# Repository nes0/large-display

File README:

PCB layout for a nominally 100mm 14 or 7 segment display including a PWM capable driver.

https://github.com/nes0/large-display

Licenced under "CERN Open Hardware Licence Version 2 - Weakly Reciprocal" http://ohwr.org/cernohl. Also see "cern_ohl_w_v2.txt"

No warranty is provided for this documentation implied or otherwise.

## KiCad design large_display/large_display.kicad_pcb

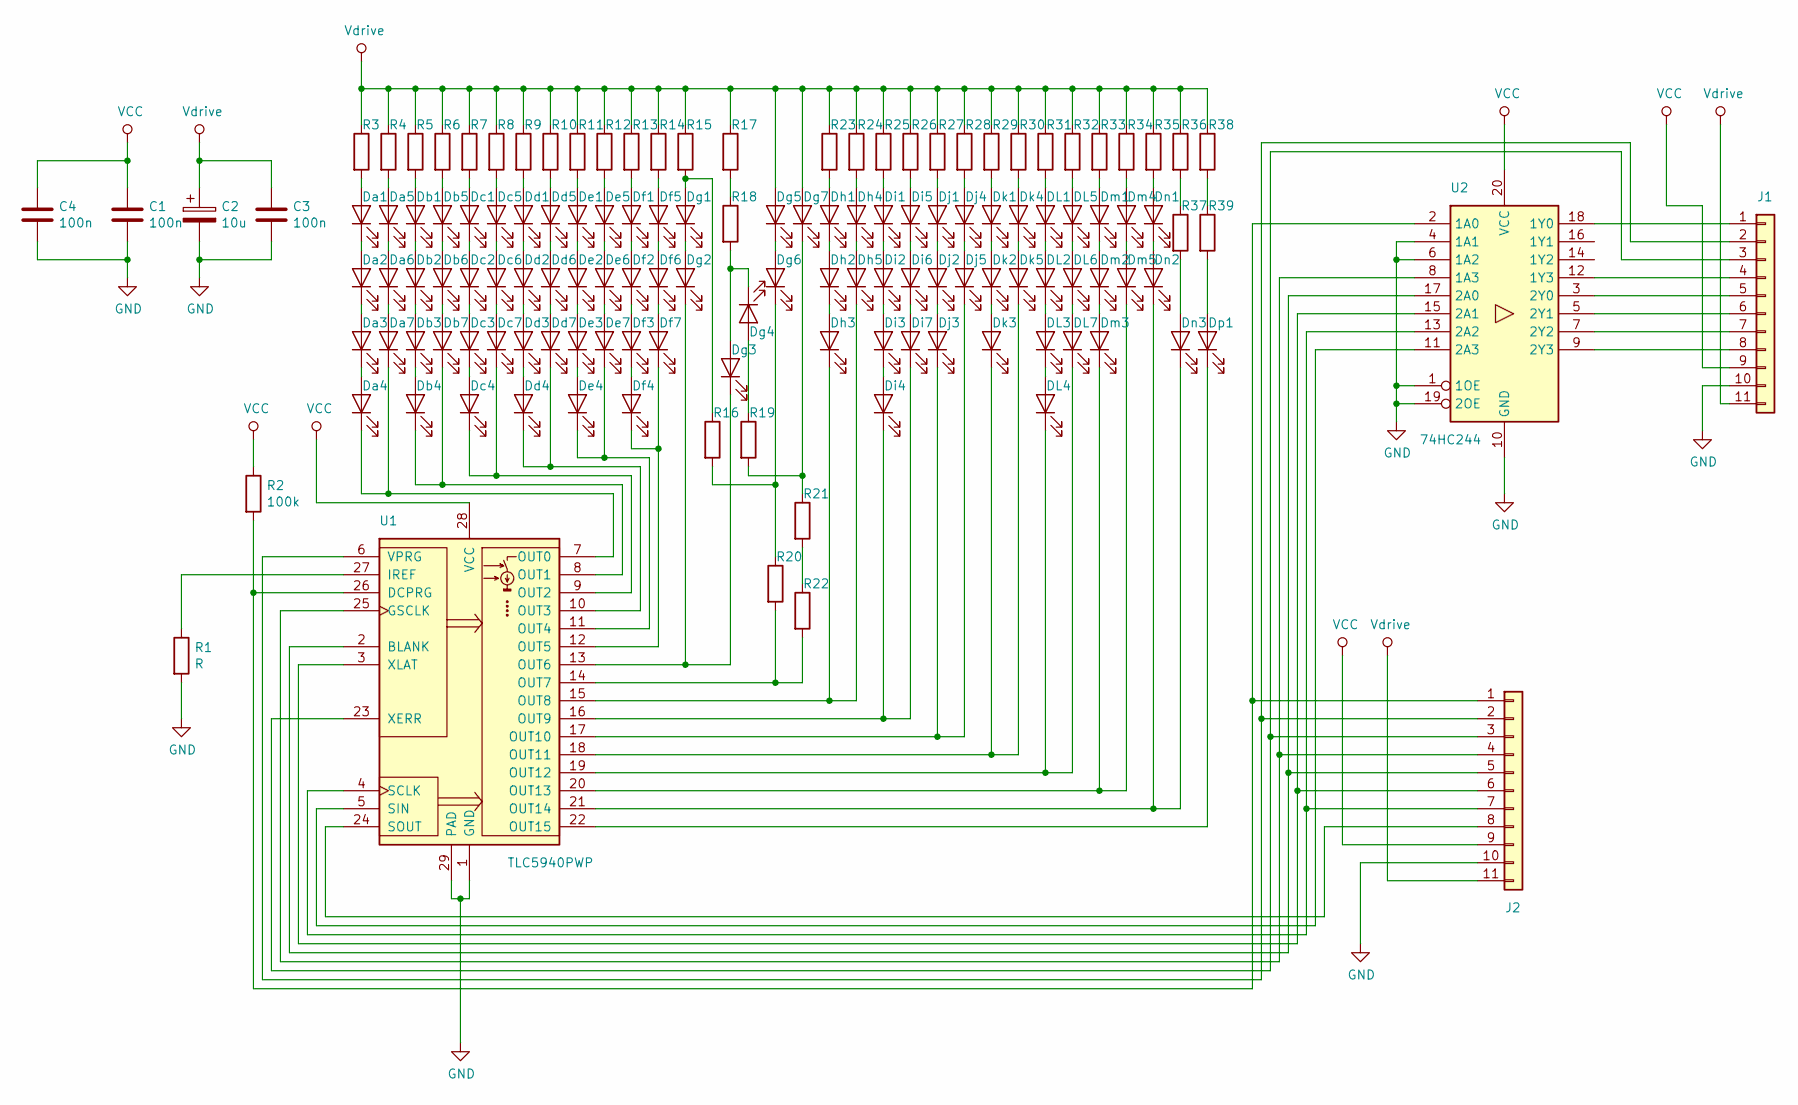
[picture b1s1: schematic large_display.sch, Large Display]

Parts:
C1, C3, C4: 100n; C_0805_2012Metric
C2: 10u; CP_Elec_6.3x4.5
DL1, DL2, DL3, DL4, DL5, DL6, DL7: LED; LED_PLCC_2835_Handsoldering
Da1, Da2, Da3, Da4, Da5, Da6, Da7: LED; LED_PLCC_2835_Handsoldering
Db1, Db2, Db3, Db4, Db5, Db6, Db7: LED; LED_PLCC_2835_Handsoldering
Dc1, Dc2, Dc3, Dc4, Dc5, Dc6, Dc7: LED; LED_PLCC_2835_Handsoldering
Dd1, Dd2, Dd3, Dd4, Dd5, Dd6, Dd7: LED; LED_PLCC_2835_Handsoldering
De1, De2, De3, De4, De5, De6, De7: LED; LED_PLCC_2835_Handsoldering
Df1, Df2, Df3, Df4, Df5, Df6, Df7: LED; LED_PLCC_2835_Handsoldering
Dg1, Dg2, Dg3, Dg4, Dg5, Dg6, Dg7: LED; LED_PLCC_2835_Handsoldering
Dh1, Dh2, Dh3, Dh4, Dh5: LED; LED_PLCC_2835_Handsoldering
Di1, Di2, Di3, Di4, Di5, Di6, Di7: LED; LED_PLCC_2835_Handsoldering
Dj1, Dj2, Dj3, Dj4, Dj5: LED; LED_PLCC_2835_Handsoldering
Dk1, Dk2, Dk3, Dk4, Dk5: LED; LED_PLCC_2835_Handsoldering
Dm1, Dm2, Dm3, Dm4, Dm5: LED; LED_PLCC_2835_Handsoldering
Dn1, Dn2, Dn3: LED; LED_PLCC_2835_Handsoldering
Dp1: LED; LED_PLCC_2835_Handsoldering
J1: Conn_01x11; PinHeader_1x11_P2.54mm_Horizontal
J2: Conn_01x11; PinSocket_1x11_P2.54mm_Horizontal
R1: R; R_0805_2012Metric_Pad1.15x1.40mm_HandSolder
R2: 100k; R_0805_2012Metric_Pad1.15x1.40mm_HandSolder
R3, R4, R5, R6, R7, R8, R9, R10, R11, R12, R13, R14, R15, R16, R17, R18, R19, R20, R21, R22, R23, R24, R25, R26, R27, R28, R29, R30, R31, R32, R33, R34, R35, R36, R37, R38, R39: R; R_1206_3216Metric_Pad1.42x1.75mm_HandSolder
U1: TLC5940PWP; HTSSOP-28-1EP_4.4x9.7mm_P0.65mm_EP3.4x9.5mm_Mask2.4x6.17mm_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
U2: 74HC244; SSOP-20_5.3x7.2mm_P0.65mm

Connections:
GND: C1.2, C2.2, C3.2, C4.2, J1.10, J2.10, R1.2, U1.1 (GND), U1.29 (PAD), U2.1 (1OE), U2.4 (1A1), U2.6 (1A2), U2.10 (GND), U2.19 (2OE)
unnamed: DL1.1 (K), DL2.2 (A)
unnamed: DL1.2 (A), R31.2
unnamed: DL2.1 (K), DL3.2 (A)
unnamed: DL3.1 (K), DL4.2 (A)
unnamed: DL4.1 (K), DL7.1 (K), U1.19 (OUT12)
unnamed: DL5.1 (K), DL6.2 (A)
unnamed: DL5.2 (A), R32.2
unnamed: DL6.1 (K), DL7.2 (A)
unnamed: Da1.1 (K), Da2.2 (A)
unnamed: Da1.2 (A), R3.2
unnamed: Da2.1 (K), Da3.2 (A)
unnamed: Da3.1 (K), Da4.2 (A)
unnamed: Da4.1 (K), Da7.1 (K), U1.7 (OUT0)
unnamed: Da5.1 (K), Da6.2 (A)
unnamed: Da5.2 (A), R4.2
unnamed: Da6.1 (K), Da7.2 (A)
unnamed: Db1.1 (K), Db2.2 (A)
unnamed: Db1.2 (A), R5.2
unnamed: Db2.1 (K), Db3.2 (A)
unnamed: Db3.1 (K), Db4.2 (A)
unnamed: Db4.1 (K), Db7.1 (K), U1.8 (OUT1)
unnamed: Db5.1 (K), Db6.2 (A)
unnamed: Db5.2 (A), R6.2
unnamed: Db6.1 (K), Db7.2 (A)
unnamed: Dc1.1 (K), Dc2.2 (A)
unnamed: Dc1.2 (A), R7.2
unnamed: Dc2.1 (K), Dc3.2 (A)
unnamed: Dc3.1 (K), Dc4.2 (A)
unnamed: Dc4.1 (K), Dc7.1 (K), U1.9 (OUT2)
unnamed: Dc5.1 (K), Dc6.2 (A)
unnamed: Dc5.2 (A), R8.2
unnamed: Dc6.1 (K), Dc7.2 (A)
unnamed: Dd1.1 (K), Dd2.2 (A)
unnamed: Dd1.2 (A), R9.2
unnamed: Dd2.1 (K), Dd3.2 (A)
unnamed: Dd3.1 (K), Dd4.2 (A)
unnamed: Dd4.1 (K), Dd7.1 (K), U1.10 (OUT3)
unnamed: Dd5.1 (K), Dd6.2 (A)
unnamed: Dd5.2 (A), R10.2
unnamed: Dd6.1 (K), Dd7.2 (A)
unnamed: De1.1 (K), De2.2 (A)
unnamed: De1.2 (A), R11.2
unnamed: De2.1 (K), De3.2 (A)
unnamed: De3.1 (K), De4.2 (A)
unnamed: De4.1 (K), De7.1 (K), U1.11 (OUT4)
unnamed: De5.1 (K), De6.2 (A)
unnamed: De5.2 (A), R12.2
unnamed: De6.1 (K), De7.2 (A)
unnamed: Df1.1 (K), Df2.2 (A)
unnamed: Df1.2 (A), R13.2
unnamed: Df2.1 (K), Df3.2 (A)
unnamed: Df3.1 (K), Df4.2 (A)
unnamed: Df4.1 (K), Df7.1 (K), U1.12 (OUT5)
unnamed: Df5.1 (K), Df6.2 (A)
unnamed: Df5.2 (A), R14.2
unnamed: Df6.1 (K), Df7.2 (A)
unnamed: Dg1.1 (K), Dg2.2 (A)
unnamed: Dg1.2 (A), R15.2, R16.1
unnamed: Dg2.1 (K), Dg3.1 (K), U1.13 (OUT6)
unnamed: Dg3.2 (A), Dg4.1 (K), R18.2
unnamed: Dg4.2 (A), R19.1
unnamed: Dg5.1 (K), Dg6.2 (A)
unnamed: Dg6.1 (K), R16.2, R20.1
unnamed: Dg7.1 (K), R19.2, R21.1
unnamed: Dh1.1 (K), Dh2.2 (A)
unnamed: Dh1.2 (A), R23.2
unnamed: Dh2.1 (K), Dh3.2 (A)
unnamed: Dh3.1 (K), Dh5.1 (K), U1.15 (OUT8)
unnamed: Dh4.1 (K), Dh5.2 (A)
unnamed: Dh4.2 (A), R24.2
unnamed: Di1.1 (K), Di2.2 (A)
unnamed: Di1.2 (A), R25.2
unnamed: Di2.1 (K), Di3.2 (A)
unnamed: Di3.1 (K), Di4.2 (A)
unnamed: Di4.1 (K), Di7.1 (K), U1.16 (OUT9)
unnamed: Di5.1 (K), Di6.2 (A)
unnamed: Di5.2 (A), R26.2
unnamed: Di6.1 (K), Di7.2 (A)
unnamed: Dj1.1 (K), Dj2.2 (A)
unnamed: Dj1.2 (A), R27.2
unnamed: Dj2.1 (K), Dj3.2 (A)
unnamed: Dj3.1 (K), Dj5.1 (K), U1.17 (OUT10)
unnamed: Dj4.1 (K), Dj5.2 (A)
unnamed: Dj4.2 (A), R28.2
unnamed: Dk1.1 (K), Dk2.2 (A)
unnamed: Dk1.2 (A), R29.2
unnamed: Dk2.1 (K), Dk3.2 (A)
unnamed: Dk3.1 (K), Dk5.1 (K), U1.18 (OUT11)
unnamed: Dk4.1 (K), Dk5.2 (A)
unnamed: Dk4.2 (A), R30.2
unnamed: Dm1.1 (K), Dm2.2 (A)
unnamed: Dm1.2 (A), R33.2
unnamed: Dm2.1 (K), Dm3.2 (A)
unnamed: Dm3.1 (K), Dm5.1 (K), U1.20 (OUT13)
unnamed: Dm4.1 (K), Dm5.2 (A)
unnamed: Dm4.2 (A), R34.2
unnamed: Dn1.1 (K), Dn2.2 (A)
unnamed: Dn1.2 (A), R35.2
unnamed: Dn2.1 (K), Dn3.1 (K), U1.21 (OUT14)
unnamed: Dn3.2 (A), R37.2
unnamed: Dp1.1 (K), U1.22 (OUT15)
unnamed: Dp1.2 (A), R39.2
unnamed: J1.1, U2.18 (1Y0)
unnamed: J1.2, J2.2, U1.6 (VPRG)
unnamed: J1.3, J2.3, U1.23 (XERR)
unnamed: J1.4, U2.12 (1Y3)
unnamed: J1.5, U2.3 (2Y0)
unnamed: J1.6, U2.5 (2Y1)
unnamed: J1.7, U2.7 (2Y2)
unnamed: J1.8, U2.9 (2Y3)
unnamed: J2.1, R2.2, U1.26 (DCPRG), U2.2 (1A0)
unnamed: J2.4, U1.25 (GSCLK), U2.8 (1A3)
unnamed: J2.5, U1.2 (BLANK), U2.17 (2A0)
unnamed: J2.6, U1.3 (XLAT), U2.15 (2A1)
unnamed: J2.7, U1.4 (SCLK), U2.13 (2A2)
unnamed: J2.8, U1.24 (SOUT)
unnamed: R1.1, U1.27 (IREF)
unnamed: R17.2, R18.1
unnamed: R20.2, R22.2, U1.14 (OUT7)
unnamed: R21.2, R22.1
unnamed: R36.2, R37.1
unnamed: R38.2, R39.1
unnamed: U1.5 (SIN), U2.11 (2A3)
VCC: C1.1, C4.1, J1.9, J2.9, R2.1, U1.28 (VCC), U2.20 (VCC)
Vdrive: C2.1, C3.1, Dg5.2 (A), Dg7.2 (A), J1.11, J2.11, R3.1, R4.1, R5.1, R6.1, R7.1, R8.1, R9.1, R10.1, R11.1, R12.1, R13.1, R14.1, R15.1, R17.1, R23.1, R24.1, R25.1, R26.1, R27.1, R28.1, R29.1, R30.1, R31.1, R32.1, R33.1, R34.1, R35.1, R36.1, R38.1

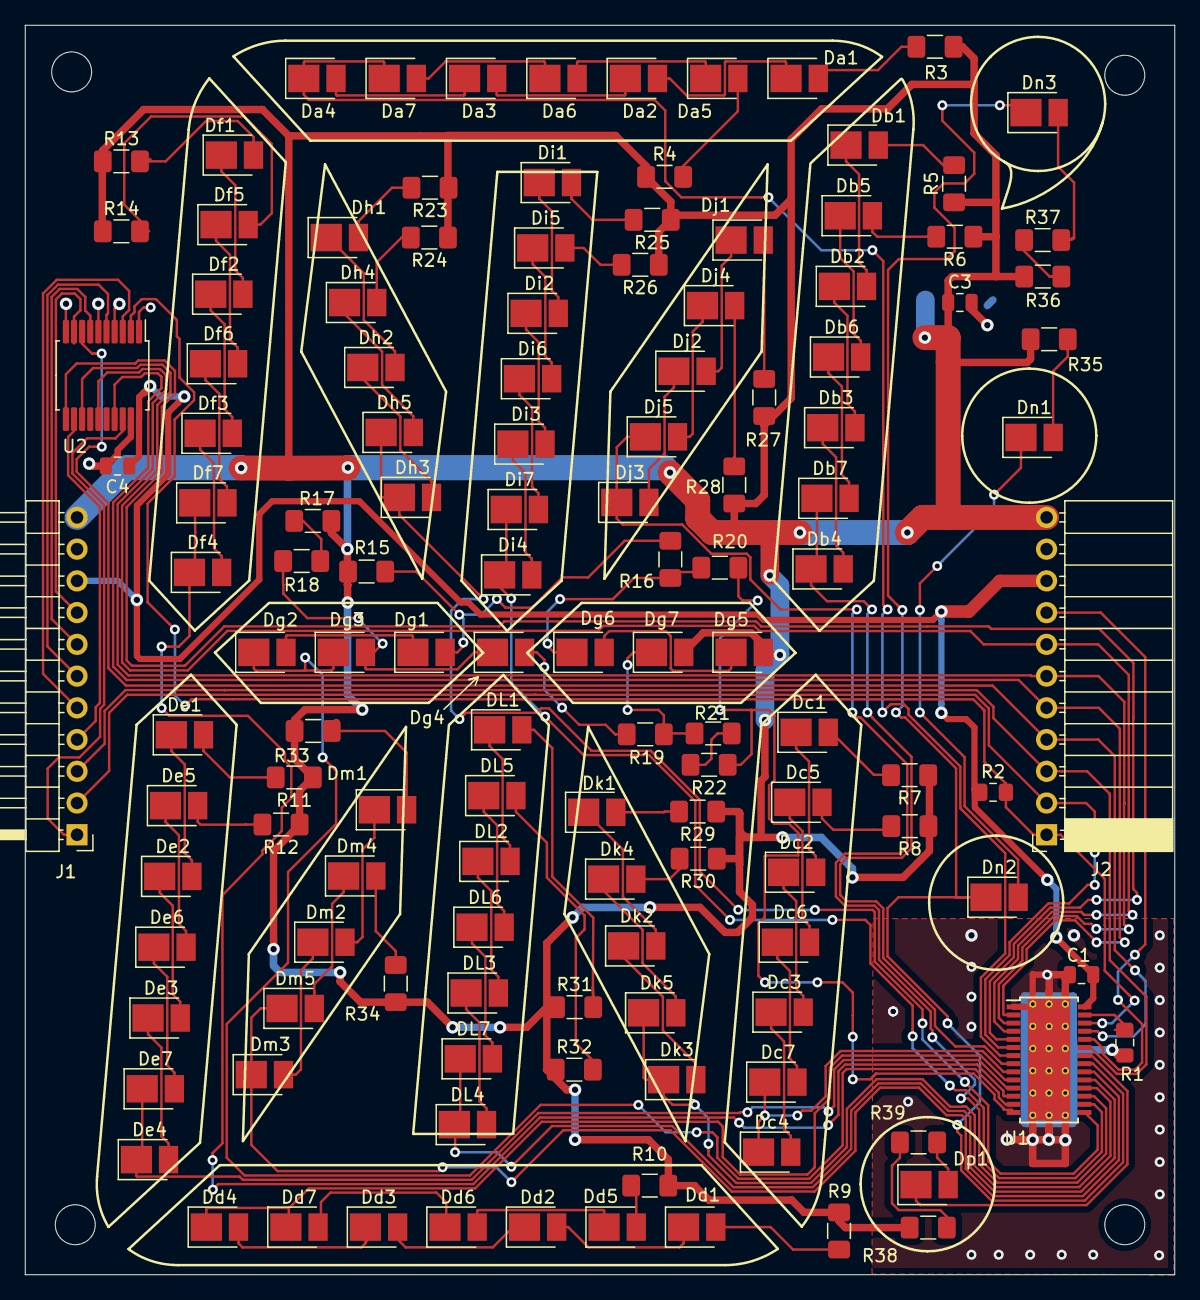
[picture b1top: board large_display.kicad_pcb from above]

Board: 2 copper layers, 92.0 x 100.0 mm, 134 parts (1 on the bottom side), 126 nets.

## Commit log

2020-11-23 initial commit: rough placement
2020-11-25 routing: first pass done
2020-11-25 first rev of layout done, text added to back silkscreen
2020-11-25 add url to silkscreen, add README, add licence
2020-11-27 Reverse Rg4 Reduce resistor size to 1206 Tidy up tracking Increase track width for VLED Fix text Add revision number
2020-11-28 Add buffering for passthru signals More tidying up of tracking
2020-11-28 add 7 segment pattern to svg diagram
2020-11-28 add decoupling for buffer IC
2020-12-01 add a bit of clearance between segment outlines and nearest components for light dam

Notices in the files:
large_display/large_display.kicad_pcb:
SPDX-License-Identifier:  CERN-OHL-W-2.0
